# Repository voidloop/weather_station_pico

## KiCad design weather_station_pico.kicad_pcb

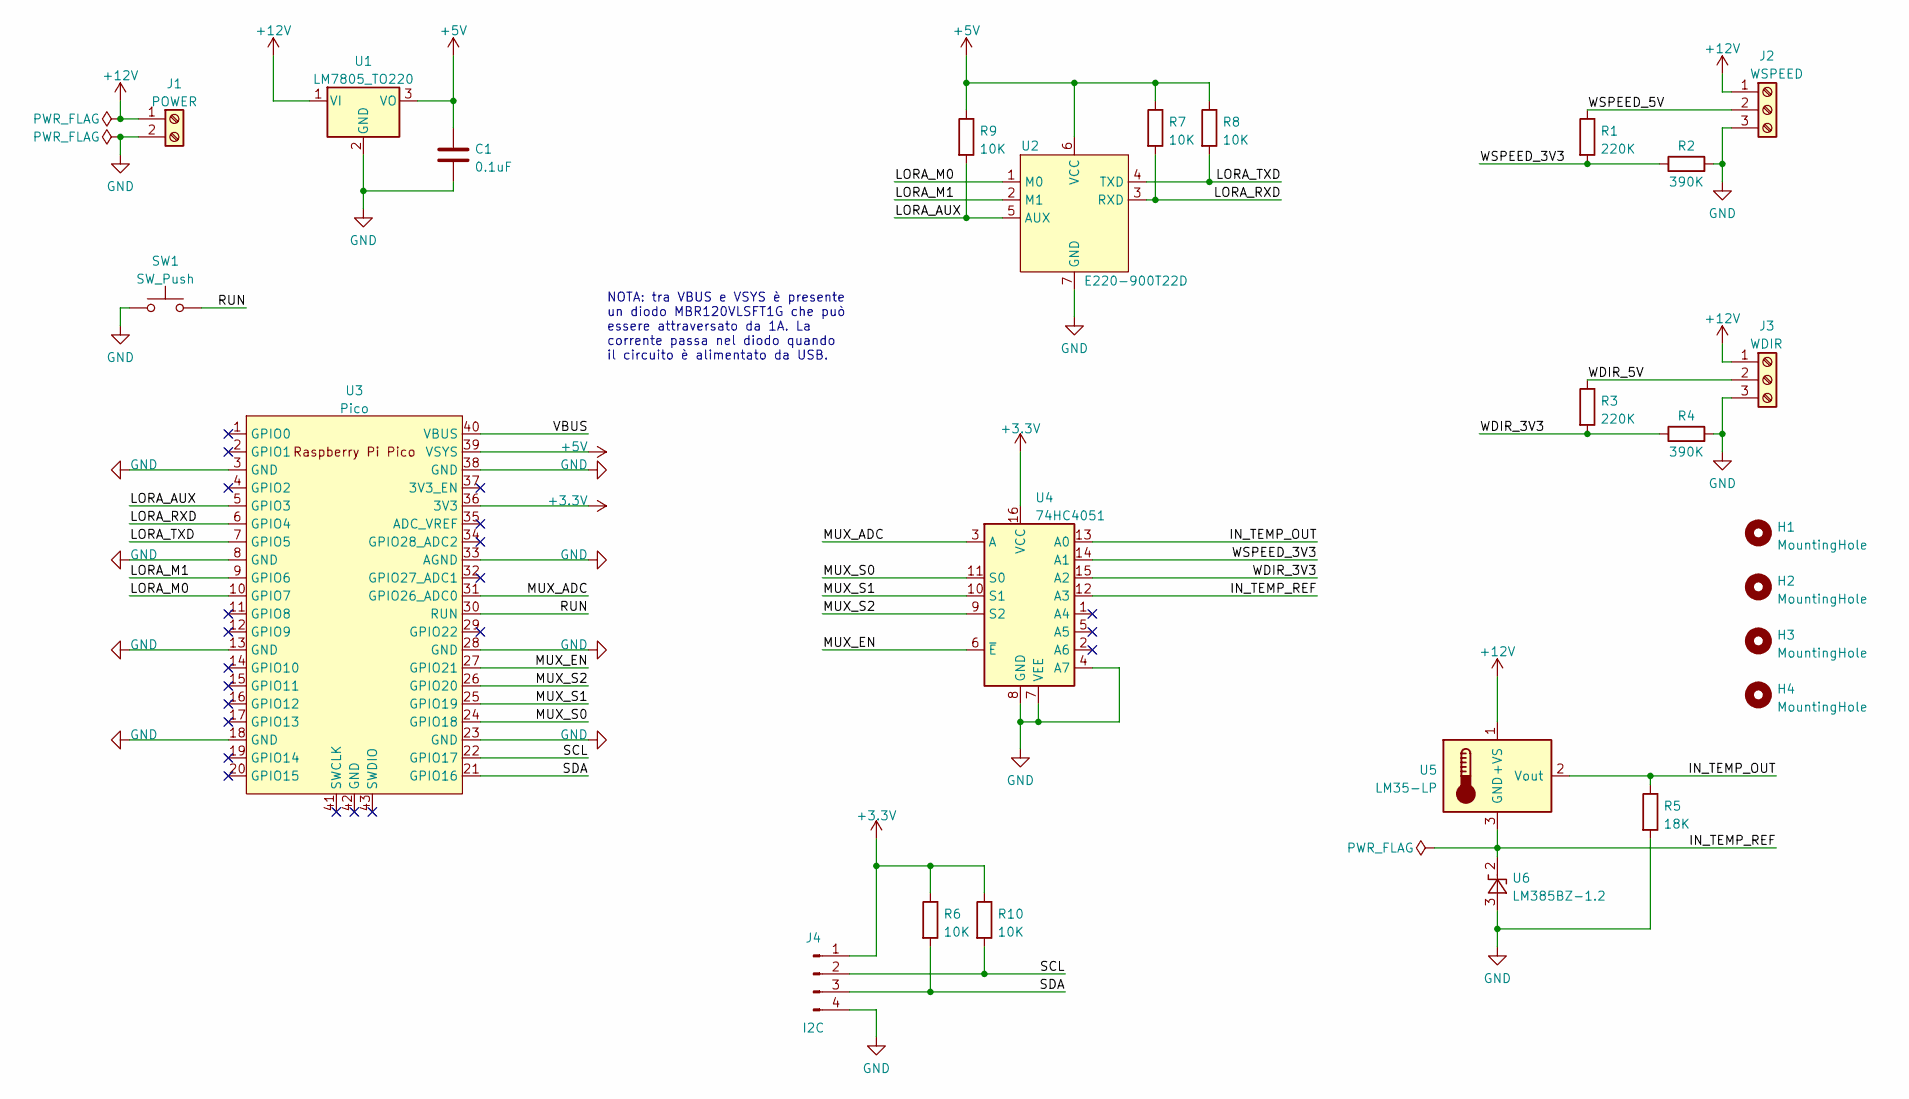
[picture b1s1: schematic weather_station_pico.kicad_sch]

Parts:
C1: 0.1uF; C_Disc_D5.0mm_W2.5mm_P5.00mm
H1, H2, H3, H4: MountingHole; MountingHole_3.2mm_M3
J1: POWER; TerminalBlock_bornier-2_P5.08mm
J2: WSPEED; TerminalBlock_TE_282834-3_1x03_P2.54mm_Horizontal
J3: WDIR; TerminalBlock_TE_282834-3_1x03_P2.54mm_Horizontal
J4: I2C; TerminalBlock_TE_282834-4_1x04_P2.54mm_Horizontal
R1, R3: 220K; R_Axial_DIN0207_L6.3mm_D2.5mm_P10.16mm_Horizontal
R2, R4: 390K; R_Axial_DIN0207_L6.3mm_D2.5mm_P10.16mm_Horizontal
R5: 18K; R_Axial_DIN0207_L6.3mm_D2.5mm_P10.16mm_Horizontal
R6, R7, R8, R9, R10: 10K; R_Axial_DIN0207_L6.3mm_D2.5mm_P10.16mm_Horizontal
SW1: SW_Push; SW_PUSH_6mm_H5mm
U1: LM7805_TO220; TO-220-3_Vertical
U2: E220-900T22D
U3: Pico; RPi_Pico_SMD_TH
U4: 74HC4051; DIP-16_W7.62mm
U5: LM35-LP; TO-92L_Inline_Wide
U6: LM385BZ-1.2; TO-92_Inline

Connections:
+3V3: J4.1, R6.1, R10.1, U3.36 (3V3), U4.16 (VCC)
+5V: C1.1, R7.1, R8.1, R9.1, U1.3 (VO), U2.6 (VCC), U3.39 (VSYS)
+12V: J1.1, J2.1, J3.1, U1.1 (VI), U5.1 (+VS)
/IN_TEMP_OUT: R5.1, U4.13 (A0), U5.2 (Vout)
/IN_TEMP_REF: U4.12 (A3), U5.3 (GND), U6.2 (K)
/LORA_AUX: R9.2, U2.5 (AUX), U3.5 (GPIO3)
/LORA_M0: U2.1 (M0), U3.10 (GPIO7)
/LORA_M1: U2.2 (M1), U3.9 (GPIO6)
/LORA_RXD: R7.2, U2.3 (RXD), U3.6 (GPIO4)
/LORA_TXD: R8.2, U2.4 (TXD), U3.7 (GPIO5)
/MUX_ADC: U3.31 (GPIO26_ADC0), U4.3 (A)
/MUX_EN: U3.27 (GPIO21), U4.6 (~E)
/MUX_S0: U3.24 (GPIO18), U4.11 (S0)
/MUX_S1: U3.25 (GPIO19), U4.10 (S1)
/MUX_S2: U3.26 (GPIO20), U4.9 (S2)
/RUN: SW1.2, U3.30 (RUN)
/SCL: J4.2, R10.2, U3.22 (GPIO17)
/SDA: J4.3, R6.2, U3.21 (GPIO16)
/VBUS: U3.40 (VBUS)
/WDIR_3V3: R3.2, R4.1, U4.15 (A2)
/WDIR_5V: J3.2, R3.1
/WSPEED_3V3: R1.2, R2.1, U4.14 (A1)
/WSPEED_5V: J2.2, R1.1
GND: C1.2, J1.2, J2.3, J3.3, J4.4, R2.2, R4.2, R5.2, SW1.1, U1.2 (GND), U2.7 (GND), U3.3 (GND), U3.8 (GND), U3.13 (GND), U3.18 (GND), U3.23 (GND), U3.28 (GND), U3.33 (AGND), U3.38 (GND), U4.4 (A7), U4.7 (VEE), U4.8 (GND), U6.3 (A)

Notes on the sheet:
NOTA: tra VBUS e VSYS è presente un diodo MBR120VLSFT1G che può essere attraversato da 1A. La corrente passa nel diodo quando il circuito è alimentato da USB.

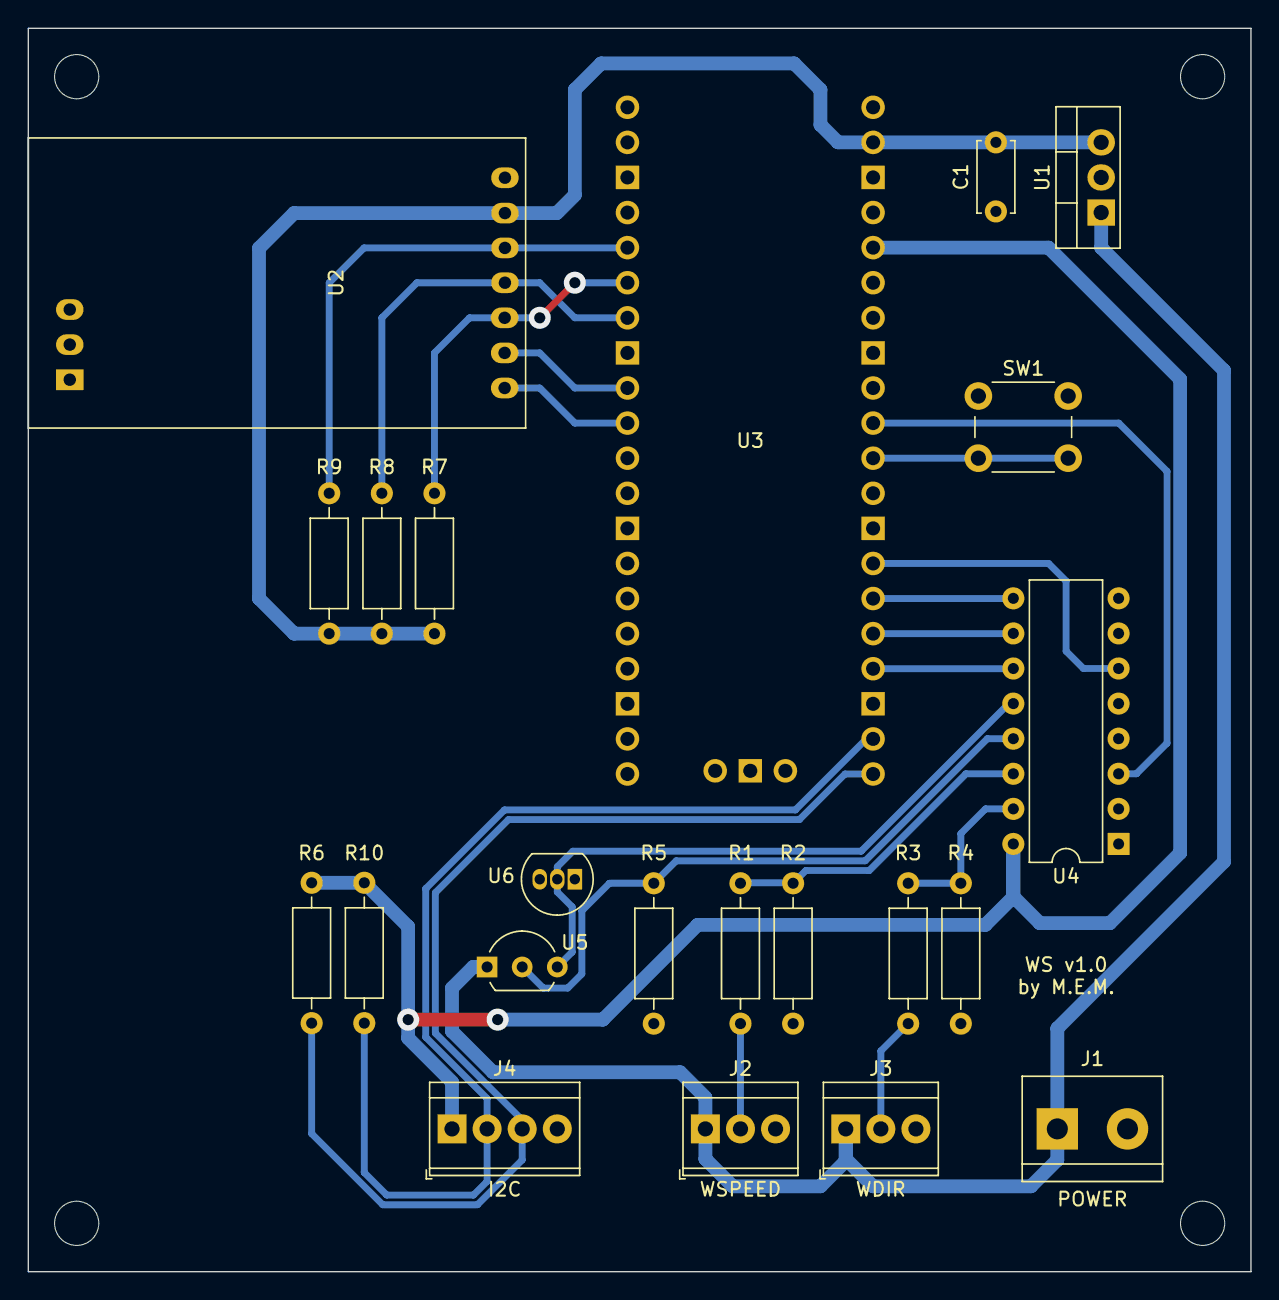
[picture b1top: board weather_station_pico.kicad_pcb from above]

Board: 2 copper layers, 88.5 x 90.0 mm, 26 parts (0 on the bottom side), 23 nets.

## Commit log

2022-04-08 update sch
2022-04-08 add some wires
2022-04-08 VSYS
2022-04-09 Add other components, add power flags.
2022-04-09 add mcp3008(?)
2022-04-13 add multiplexer and some footprints
2022-04-16 add i2c
2022-04-16 add i2c pull-up resistors
2022-04-16 ready for plot
2022-04-16 remove a via
2022-04-17 replace power connector
2022-04-17 add terminal, remove jst connector
2022-04-17 move capacitor, more simple track
2022-04-17 move lora border
2022-05-08 add millproject
